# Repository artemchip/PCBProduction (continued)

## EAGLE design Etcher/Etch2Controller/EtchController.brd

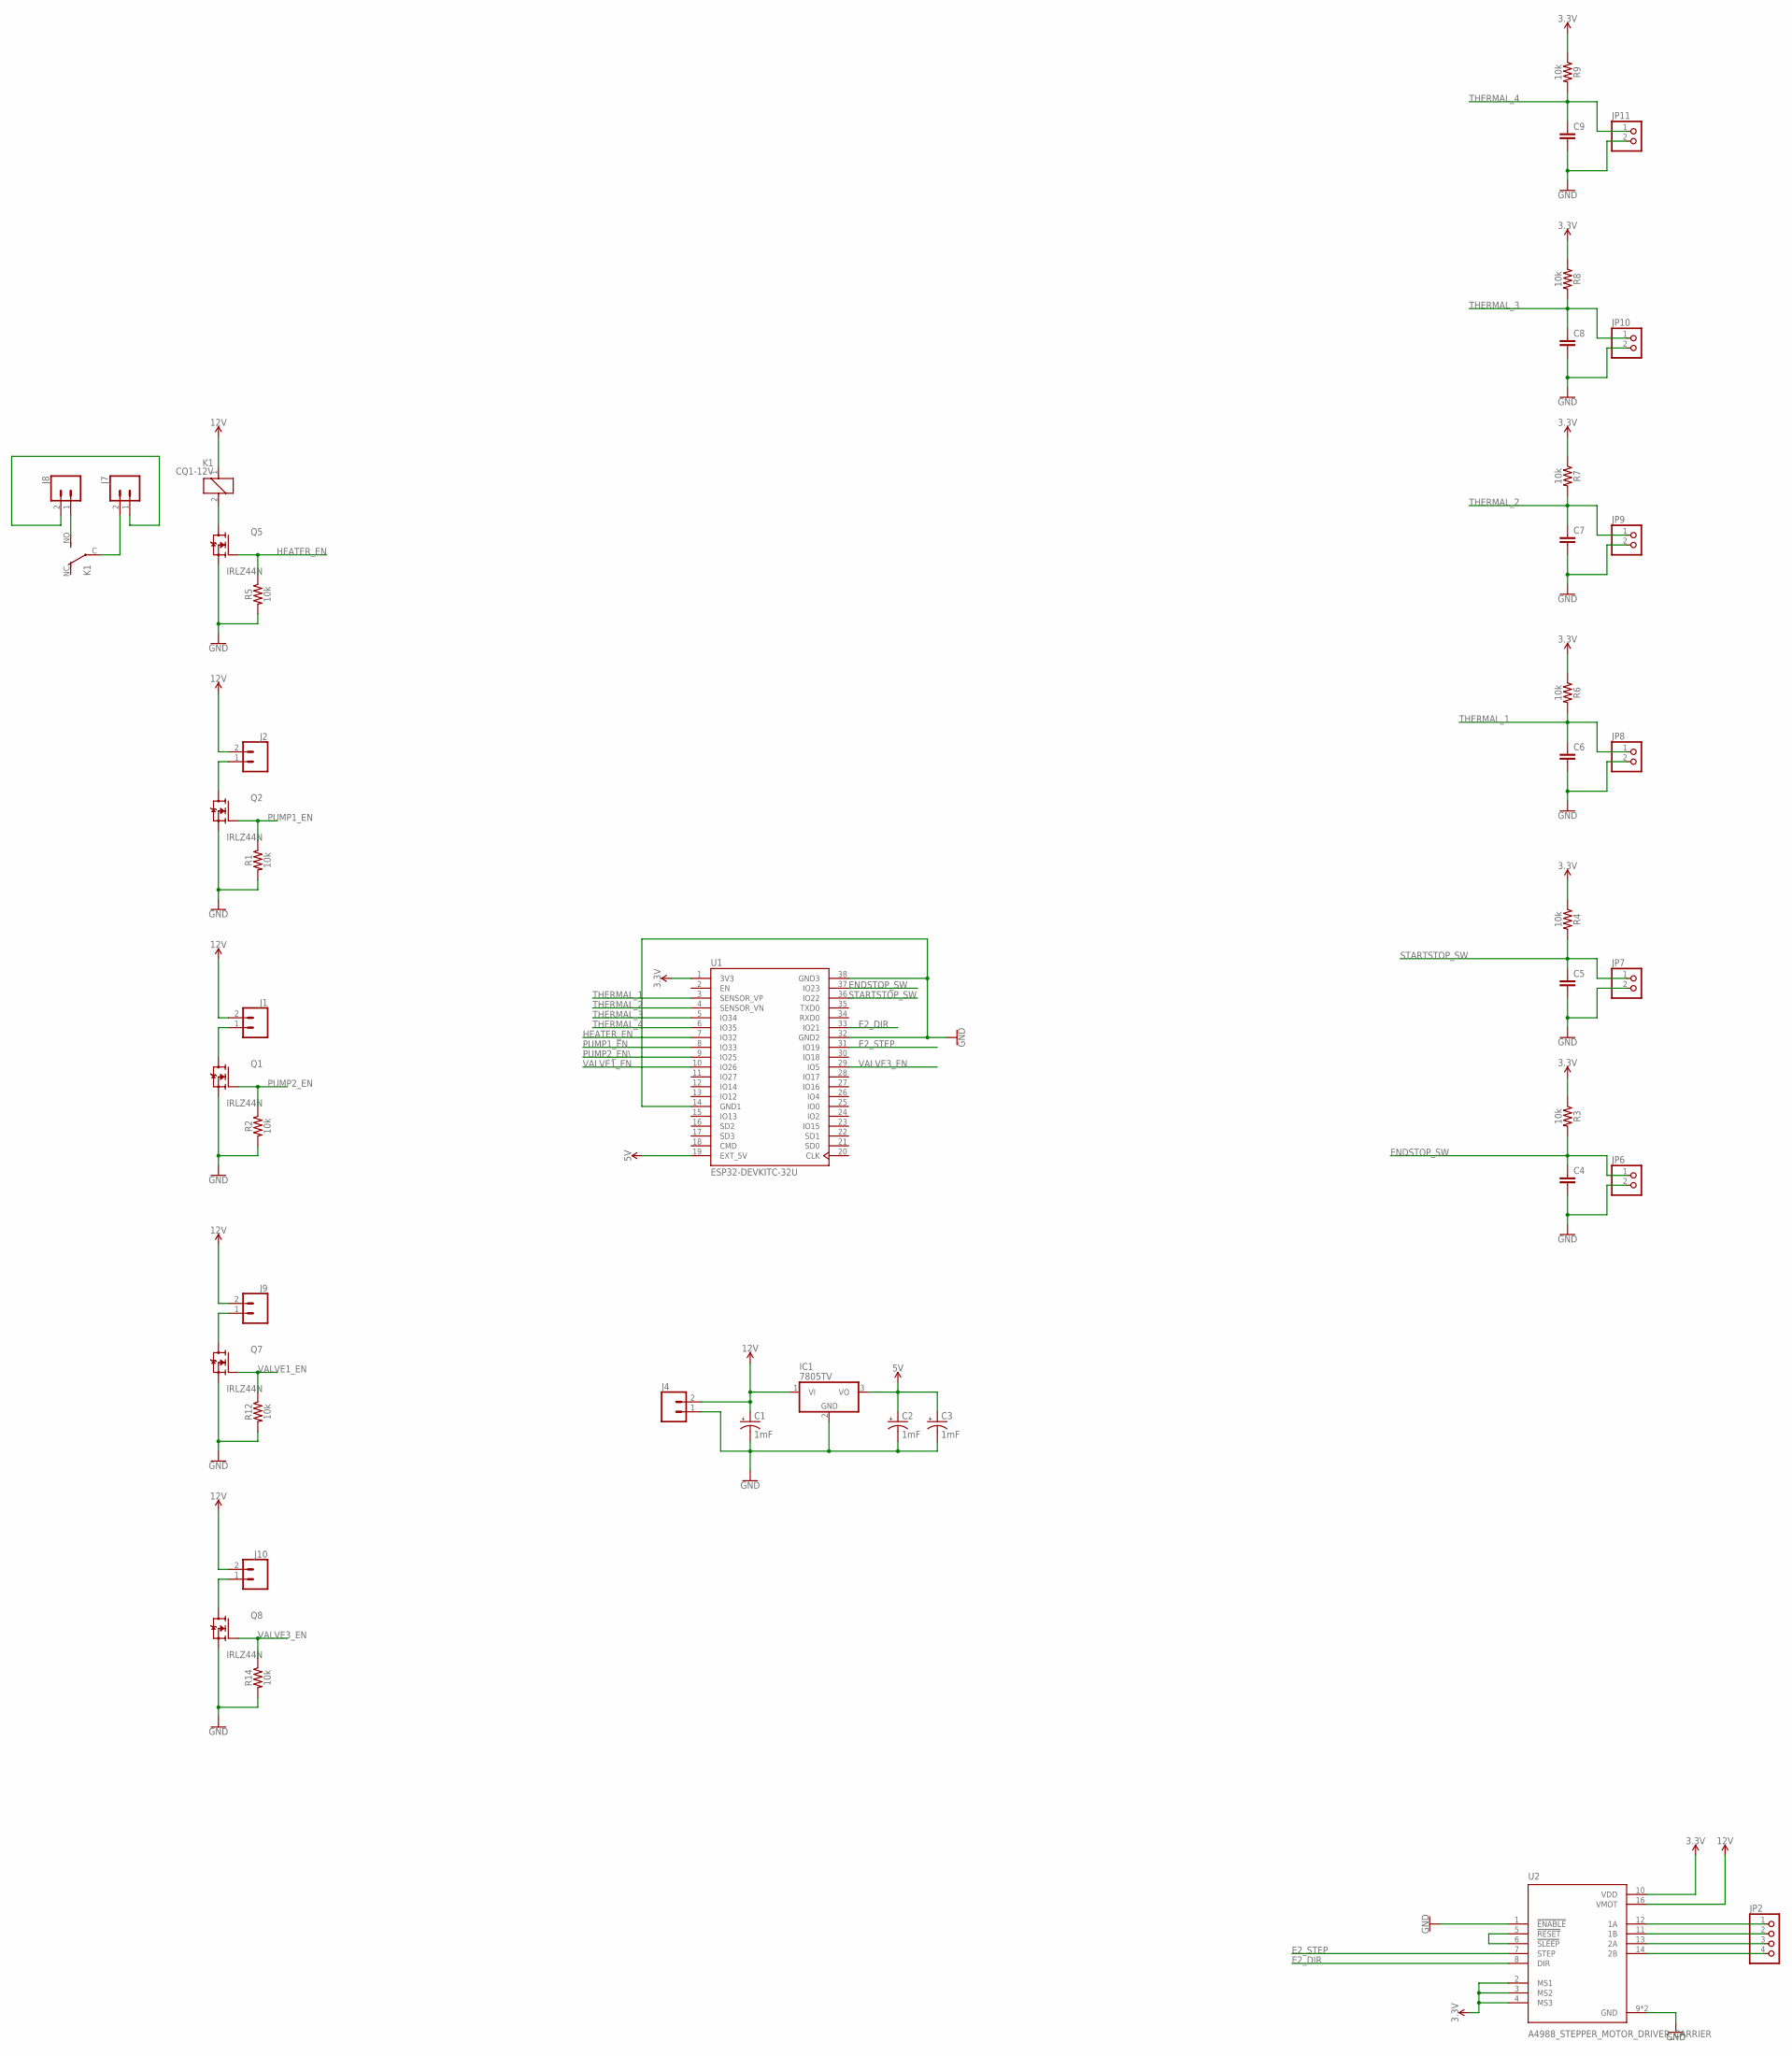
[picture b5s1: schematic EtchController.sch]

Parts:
C1, C2, C3: 1mF; CPOL-RADIAL-5MM-10MM
C4, C5, C6, C7, C8, C9: C2,5-3; C2.5-3
IC1: 7805TV; TO220V
J1, J2, J9, J10: CONN_023.5MM; SCREWTERMINAL-3.5MM-2
J4: CONN_023.5MM-NO_SILK; SCREWTERMINAL-3.5MM-2-NS
J7, J8: CONN_025MM; SCREWTERMINAL-5MM-2
JP2: PINHD-1X4; 1X04
JP6, JP7, JP8, JP9, JP10, JP11: PINHD-1X2; 1X02
K1: CQ1-12V; CQ1
Q1, Q2, Q5, Q7, Q8: IRLZ44N; TO254P1054X469X1930-3
R1, R2, R3, R4, R5, R6, R7, R8, R9, R12, R14: 10k; AXIAL-0.1
U1: ESP32-DEVKITC-32U; MODULE_ESP32-DEVKITC-32U
U2: A4988_STEPPER_MOTOR_DRIVER_CARRIER; MODULE_A4988_STEPPER_MOTOR_DRIVER_CARRIER

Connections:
3.3V: R3.P$1 (1), R4.P$1 (1), R6.P$1 (1), R7.P$1 (1), R8.P$1 (1), R9.P$1 (1), U1.1 (3V3), U2.2 (MS1), U2.3 (MS2), U2.4 (MS3), U2.10 (VDD)
5V: C2.+, C3.+, IC1.3 (VO), U1.19 (EXT_5V)
12V: C1.+, IC1.1 (VI), J1.2, J2.2, J4.2, J9.2, J10.2, K1.1, U2.16 (VMOT)
E2_DIR: U1.33 (IO21), U2.8 (DIR)
E2_STEP: U1.31 (IO19), U2.7 (STEP)
ENDSTOP_SW: C4.1, JP6.1, R3.P$2 (2), U1.37 (IO23)
GND: C1.-, C2.-, C3.-, C4.2, C5.2, C6.2, C7.2, C8.2, C9.2, IC1.2 (GND), J4.1, JP6.2, JP7.2, JP8.2, JP9.2, JP10.2, JP11.2, Q1.3 (S), Q2.3 (S), Q5.3 (S), Q7.3 (S), Q8.3 (S), R1.P$2 (2), R2.P$2 (2), R5.P$2 (2), R12.P$2 (2), R14.P$2 (2), U1.14 (GND1), U1.32 (GND2), U1.38 (GND3), U2.1 (!ENABLE), U2.9 (GND), U2.15 (GND)
HEATER_EN: Q5.1 (G), R5.P$1 (1), U1.7 (IO32)
unnamed: JP2.1, U2.12 (1A)
unnamed: JP2.2, U2.11 (1B)
unnamed: J2.1, Q2.2 (D)
unnamed: J1.1, Q1.2 (D)
unnamed: J8.1, K1.NO (S)
unnamed: J7.2, K1.C
unnamed: JP2.3, U2.13 (2A)
unnamed: K1.2, Q5.2 (D)
unnamed: J7.1, J8.2
unnamed: JP2.4, U2.14 (2B)
unnamed: U2.5 (!RESET), U2.6 (!SLEEP)
unnamed: J9.1, Q7.2 (D)
unnamed: J10.1, Q8.2 (D)
PUMP1_EN: Q2.1 (G), R1.P$1 (1), U1.8 (IO33)
PUMP2_EN: Q1.1 (G), R2.P$1 (1)
PUMP2_EN\: U1.9 (IO25)
STARTSTOP_SW: C5.1, JP7.1, R4.P$2 (2), U1.36 (IO22)
THERMAL_1: C6.1, JP8.1, R6.P$2 (2), U1.3 (SENSOR_VP)
THERMAL_2: C7.1, JP9.1, R7.P$2 (2), U1.4 (SENSOR_VN)
THERMAL_3: C8.1, JP10.1, R8.P$2 (2), U1.5 (IO34)
THERMAL_4: C9.1, JP11.1, R9.P$2 (2), U1.6 (IO35)
VALVE1_EN: Q7.1 (G), R12.P$1 (1), U1.10 (IO26)
VALVE3_EN: Q8.1 (G), R14.P$1 (1), U1.29 (IO5)

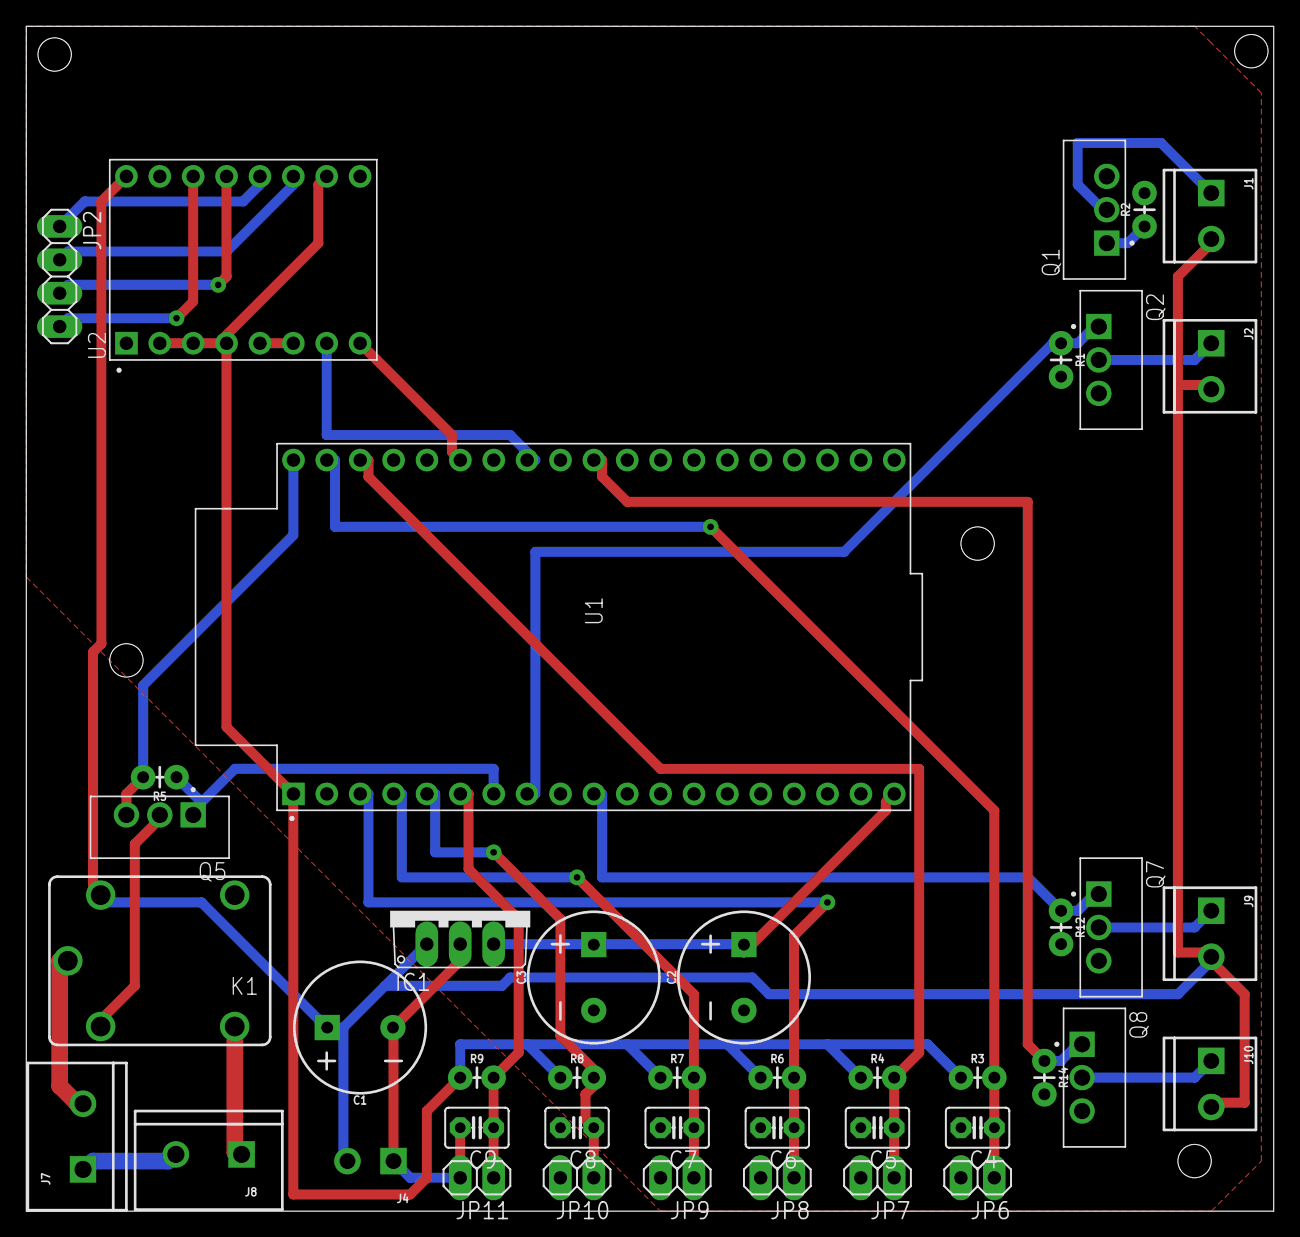
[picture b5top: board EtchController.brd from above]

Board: 2 copper layers, 94.9 x 90.2 mm, 43 parts (0 on the bottom side), 30 nets.
